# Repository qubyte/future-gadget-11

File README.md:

# FG-11 split keyboard

This repository uses kicad 5 and git submodules for dependencies.

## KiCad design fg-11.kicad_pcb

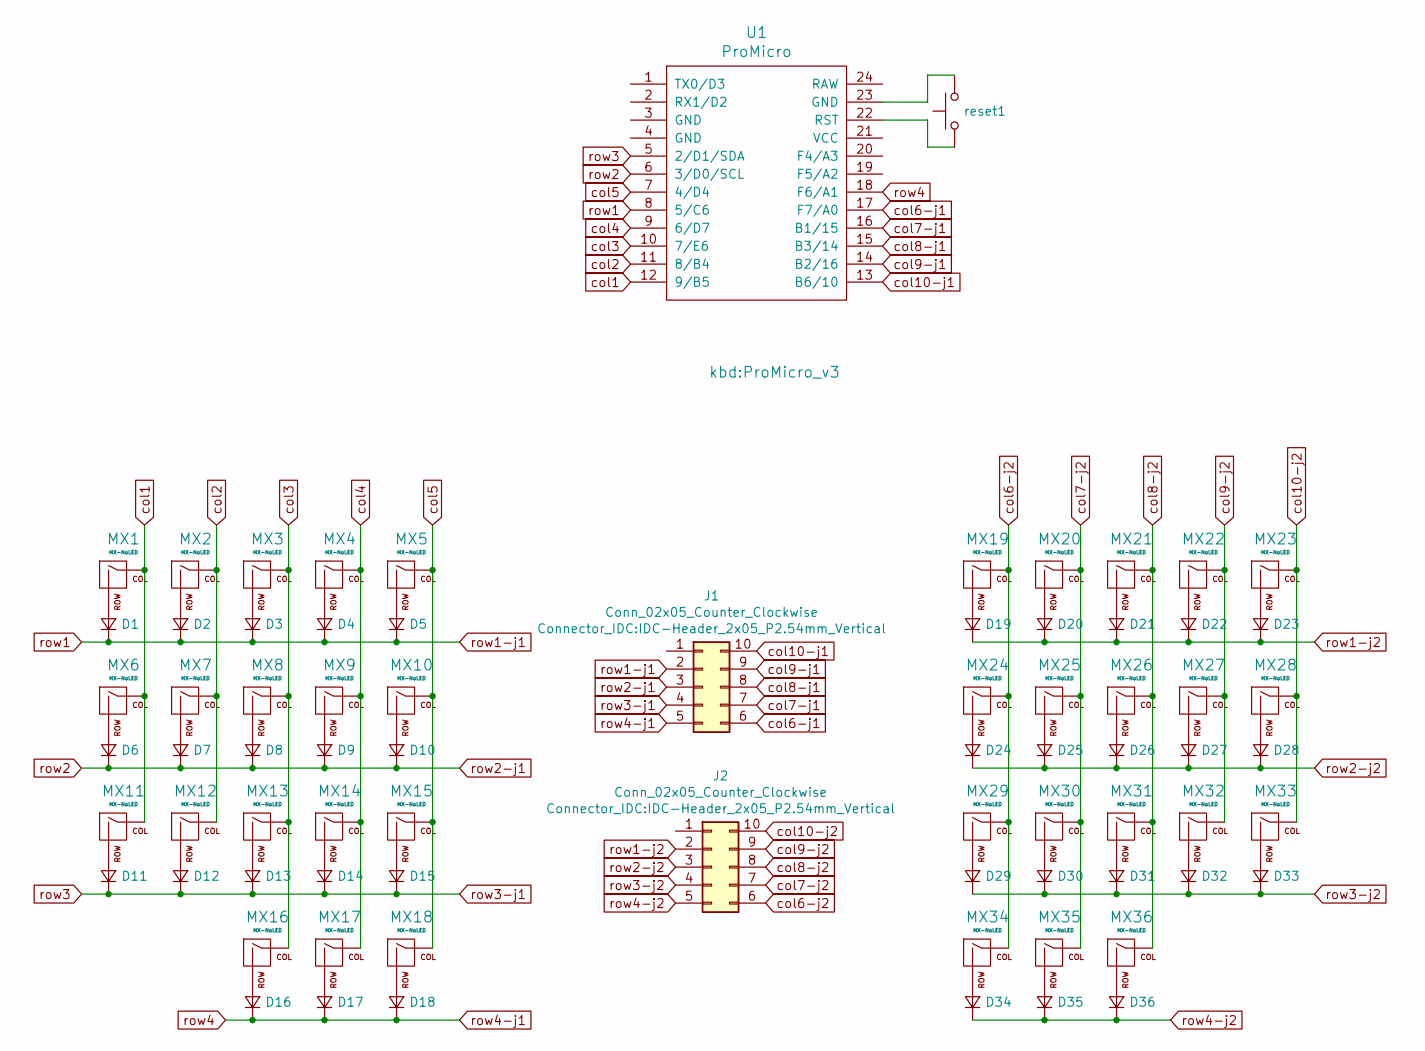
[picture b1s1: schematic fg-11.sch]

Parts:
D1, D2, D3, D4, D5, D6, D7, D8, D9, D10, D11, D12, D13, D14, D15, D16, D17, D18, D19, D20, D21, D22, D23, D24, D25, D26, D27, D28, D29, D30, D31, D32, D33, D34, D35, D36: D_Small; D_SOD-123
J1, J2: Conn_02x05_Counter_Clockwise; IDC-Header_2x05_P2.54mm_Vertical
MX1, MX2, MX3, MX4, MX5, MX6, MX7, MX8, MX9, MX10, MX11, MX12, MX13, MX14, MX15, MX16, MX17, MX18, MX19, MX20, MX21, MX22, MX23, MX24, MX25, MX26, MX27, MX28, MX29, MX30, MX31, MX32, MX33, MX34, MX35, MX36: MX-NoLED; ChocV1_V2_Hotswap
U1: ProMicro; ProMicro_v3
reset1: SW_Push; ResetSW_1side

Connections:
unnamed: D1.2 (A), MX1.2 (ROW)
unnamed: D2.2 (A), MX2.2 (ROW)
unnamed: D3.2 (A), MX3.2 (ROW)
unnamed: D4.2 (A), MX4.2 (ROW)
unnamed: D5.2 (A), MX5.2 (ROW)
unnamed: D6.2 (A), MX6.2 (ROW)
unnamed: D7.2 (A), MX7.2 (ROW)
unnamed: D8.2 (A), MX8.2 (ROW)
unnamed: D9.2 (A), MX9.2 (ROW)
unnamed: D10.2 (A), MX10.2 (ROW)
unnamed: D11.2 (A), MX11.2 (ROW)
unnamed: D12.2 (A), MX12.2 (ROW)
unnamed: D13.2 (A), MX13.2 (ROW)
unnamed: D14.2 (A), MX14.2 (ROW)
unnamed: D15.2 (A), MX15.2 (ROW)
unnamed: D16.2 (A), MX16.2 (ROW)
unnamed: D17.2 (A), MX17.2 (ROW)
unnamed: D18.2 (A), MX18.2 (ROW)
unnamed: D19.2 (A), MX19.2 (ROW)
unnamed: D20.2 (A), MX20.2 (ROW)
unnamed: D21.2 (A), MX21.2 (ROW)
unnamed: D22.2 (A), MX22.2 (ROW)
unnamed: D23.2 (A), MX23.2 (ROW)
unnamed: D24.2 (A), MX24.2 (ROW)
unnamed: D25.2 (A), MX25.2 (ROW)
unnamed: D26.2 (A), MX26.2 (ROW)
unnamed: D27.2 (A), MX27.2 (ROW)
unnamed: D28.2 (A), MX28.2 (ROW)
unnamed: D29.2 (A), MX29.2 (ROW)
unnamed: D30.2 (A), MX30.2 (ROW)
unnamed: D31.2 (A), MX31.2 (ROW)
unnamed: D32.2 (A), MX32.2 (ROW)
unnamed: D33.2 (A), MX33.2 (ROW)
unnamed: D34.2 (A), MX34.2 (ROW)
unnamed: D35.2 (A), MX35.2 (ROW)
unnamed: D36.2 (A), MX36.2 (ROW)
unnamed: U1.22 (RST), reset1.1
unnamed: U1.23 (GND), reset1.2
col1: MX1.1 (COL), MX6.1 (COL), MX11.1 (COL), U1.12 (9/B5)
col2: MX2.1 (COL), MX7.1 (COL), MX12.1 (COL), U1.11 (8/B4)
col3: MX3.1 (COL), MX8.1 (COL), MX13.1 (COL), MX16.1 (COL), U1.10 (7/E6)
col4: MX4.1 (COL), MX9.1 (COL), MX14.1 (COL), MX17.1 (COL), U1.9 (6/D7)
col5: MX5.1 (COL), MX10.1 (COL), MX15.1 (COL), MX18.1 (COL), U1.7 (4/D4)
col6-j1: J1.6, U1.17 (F7/A0)
col6-j2: J2.6, MX19.1 (COL), MX24.1 (COL), MX29.1 (COL), MX34.1 (COL)
col7-j1: J1.7, U1.16 (B1/15)
col7-j2: J2.7, MX20.1 (COL), MX25.1 (COL), MX30.1 (COL), MX35.1 (COL)
col8-j1: J1.8, U1.15 (B3/14)
col8-j2: J2.8, MX21.1 (COL), MX26.1 (COL), MX31.1 (COL), MX36.1 (COL)
col9-j1: J1.9, U1.14 (B2/16)
col9-j2: J2.9, MX22.1 (COL), MX27.1 (COL), MX32.1 (COL)
col10-j1: J1.10, U1.13 (B6/10)
col10-j2: J2.10, MX23.1 (COL), MX28.1 (COL), MX33.1 (COL)
row1: D1.1 (K), D2.1 (K), D3.1 (K), D4.1 (K), D5.1 (K), J1.2, U1.8 (5/C6)
row1-j2: D19.1 (K), D20.1 (K), D21.1 (K), D22.1 (K), D23.1 (K), J2.2
row2: D6.1 (K), D7.1 (K), D8.1 (K), D9.1 (K), D10.1 (K), J1.3, U1.6 (3/D0/SCL)
row2-j2: D24.1 (K), D25.1 (K), D26.1 (K), D27.1 (K), D28.1 (K), J2.3
row3: D11.1 (K), D12.1 (K), D13.1 (K), D14.1 (K), D15.1 (K), J1.4, U1.5 (2/D1/SDA)
row3-j2: D29.1 (K), D30.1 (K), D31.1 (K), D32.1 (K), D33.1 (K), J2.4
row4: D16.1 (K), D17.1 (K), D18.1 (K), J1.5, U1.18 (F6/A1)
row4-j2: D34.1 (K), D35.1 (K), D36.1 (K), J2.5

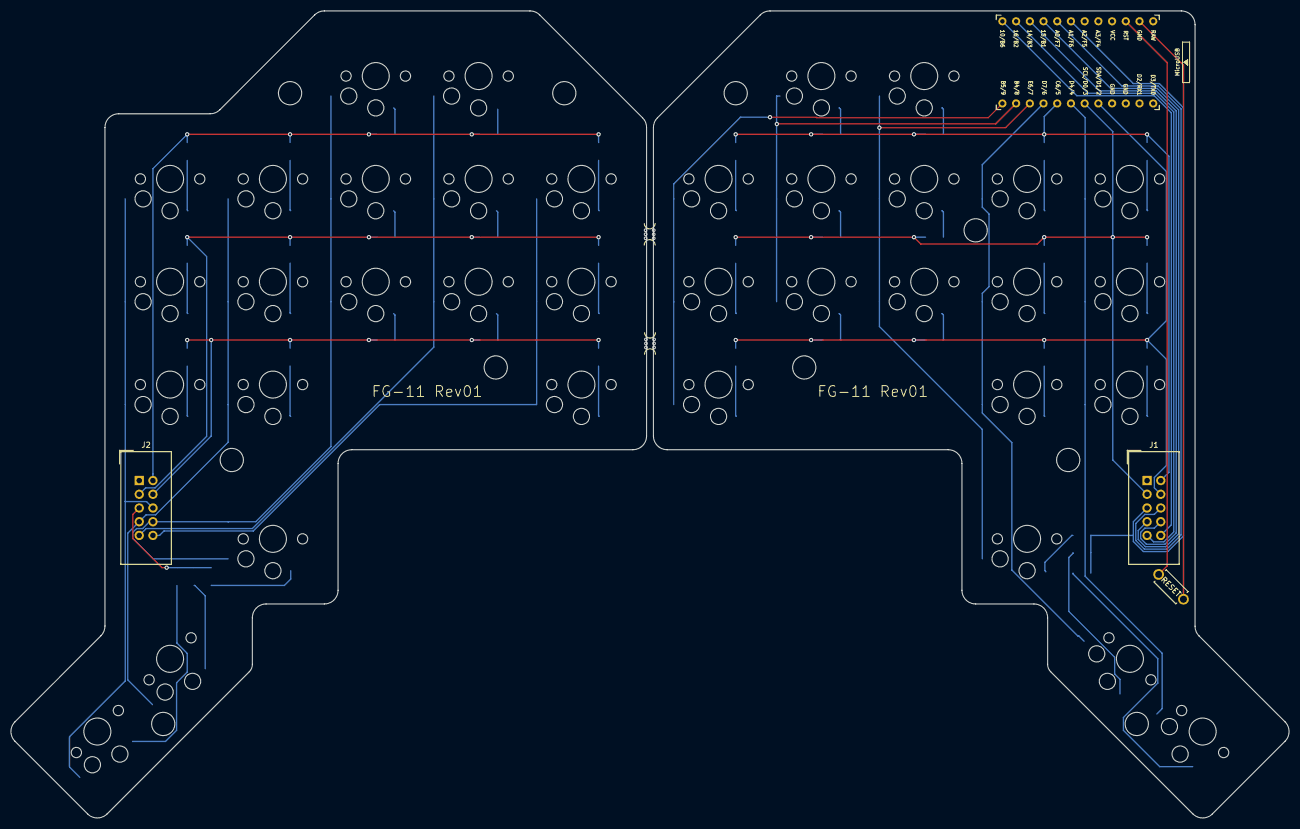
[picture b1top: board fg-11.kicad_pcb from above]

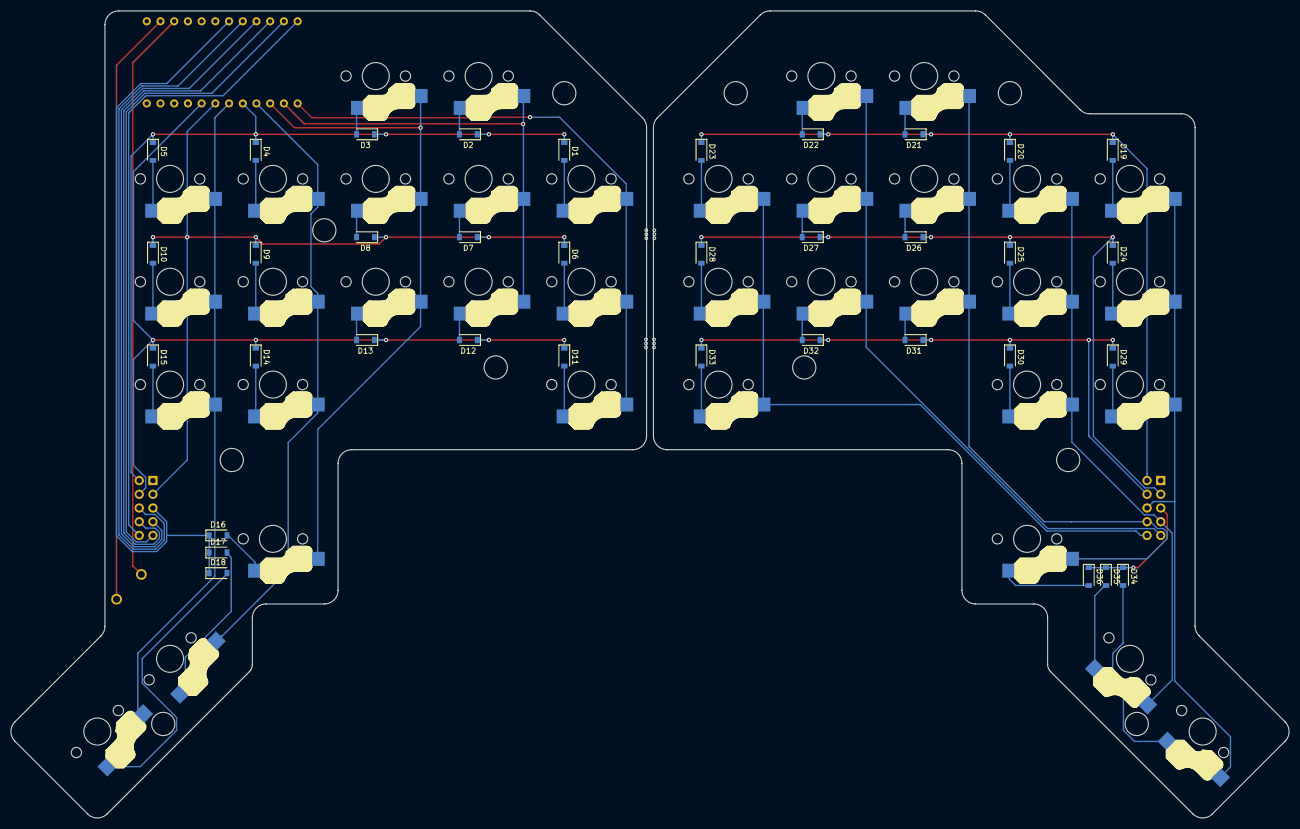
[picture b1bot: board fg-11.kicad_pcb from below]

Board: 2 copper layers, 236.8 x 149.5 mm, 88 parts (41 on the bottom side), 61 nets.

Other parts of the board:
Ref**: Val**; spacer_m2
Ref**#2, Ref**#3, Ref**#4, Ref**#5, Ref**#6, Ref**#7, Ref**#8, Ref**#9, Ref**#10: Val**; spacer_m2
mouse-bite-2mm-slot, mouse-bite-2mm-slot#2: VAL**; mouse-bite-2mm-slot

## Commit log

2022-09-19 First pass.
2022-09-20 Correct order of right thumb switches and reroute tracks to simplify.
2022-09-20 Adds readme file.
2022-09-25 Various improvements.
    - Reduce the spacing between the keys.
    - Flip the pro-micro footprint (to reveal reset buttons for elite-c etc.)
    - Rework the tracks to simplify them.
    - Redo the cuts to make them more consistent.
2022-09-25 Add mount holes, plate, and back.
2022-09-25 Last commit with plates.
2022-09-26 Panelize PCB and add SVG files for plates.
2022-10-22 First go at revision 2.
    Revision 2 has several goals:
    - Shift the index and ring finger one column outward, giving the
    index finger two columns each and the little fingers one each.
    - Flip the controller. It was handy to have it the other way up for
    access to the reset button on an elite-c, but the on-board LED
    is bright blue and distracting.
